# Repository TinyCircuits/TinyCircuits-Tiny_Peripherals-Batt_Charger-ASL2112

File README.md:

# TinyCircuits Tiny Peripheral Battery Charger
# ASL2112 Rev2

The design files are located under design_files/ for the TinyCircuits ASL2112 Rev 2 PCB.  This is a Tiny peripheral board that has a Lithium battery charger and JST SH connector.

Format is in Cadsoft Eagle format - Eagle version 6.2 was used for the original design.

For more infomation on this, check out the product page at TinyCircuits.com: https://tinycircuits.com/collections/accessories/products/tiny-battery-charger

# License:

Design by TinyCircuits.
All design files are released under the Creative Commons Attribution Share-Alike 3.0 License, see the following link for details: http://creativecommons.org/licenses/by-sa/3.0

All text above must be included in any redistribution or derived design

This project uses designs and concepts developed as part of the Arduino project and the LilyPad project.  The TinyCircuits design files themselves (schematics, PCB and libraries) are not directly derived from these works' design files and have been created new, however the concepts and basic architecture behind the TinyDuino and TinyLily products are derived and we thank the hard work of the organizations below for their contributions to open-source hardware:
  
Original Arduino Uno Design by Team Arduino

LilyPad Arduino Design by Leah Buechley and Sparkfun Electronics

Please support the open-source hardware community

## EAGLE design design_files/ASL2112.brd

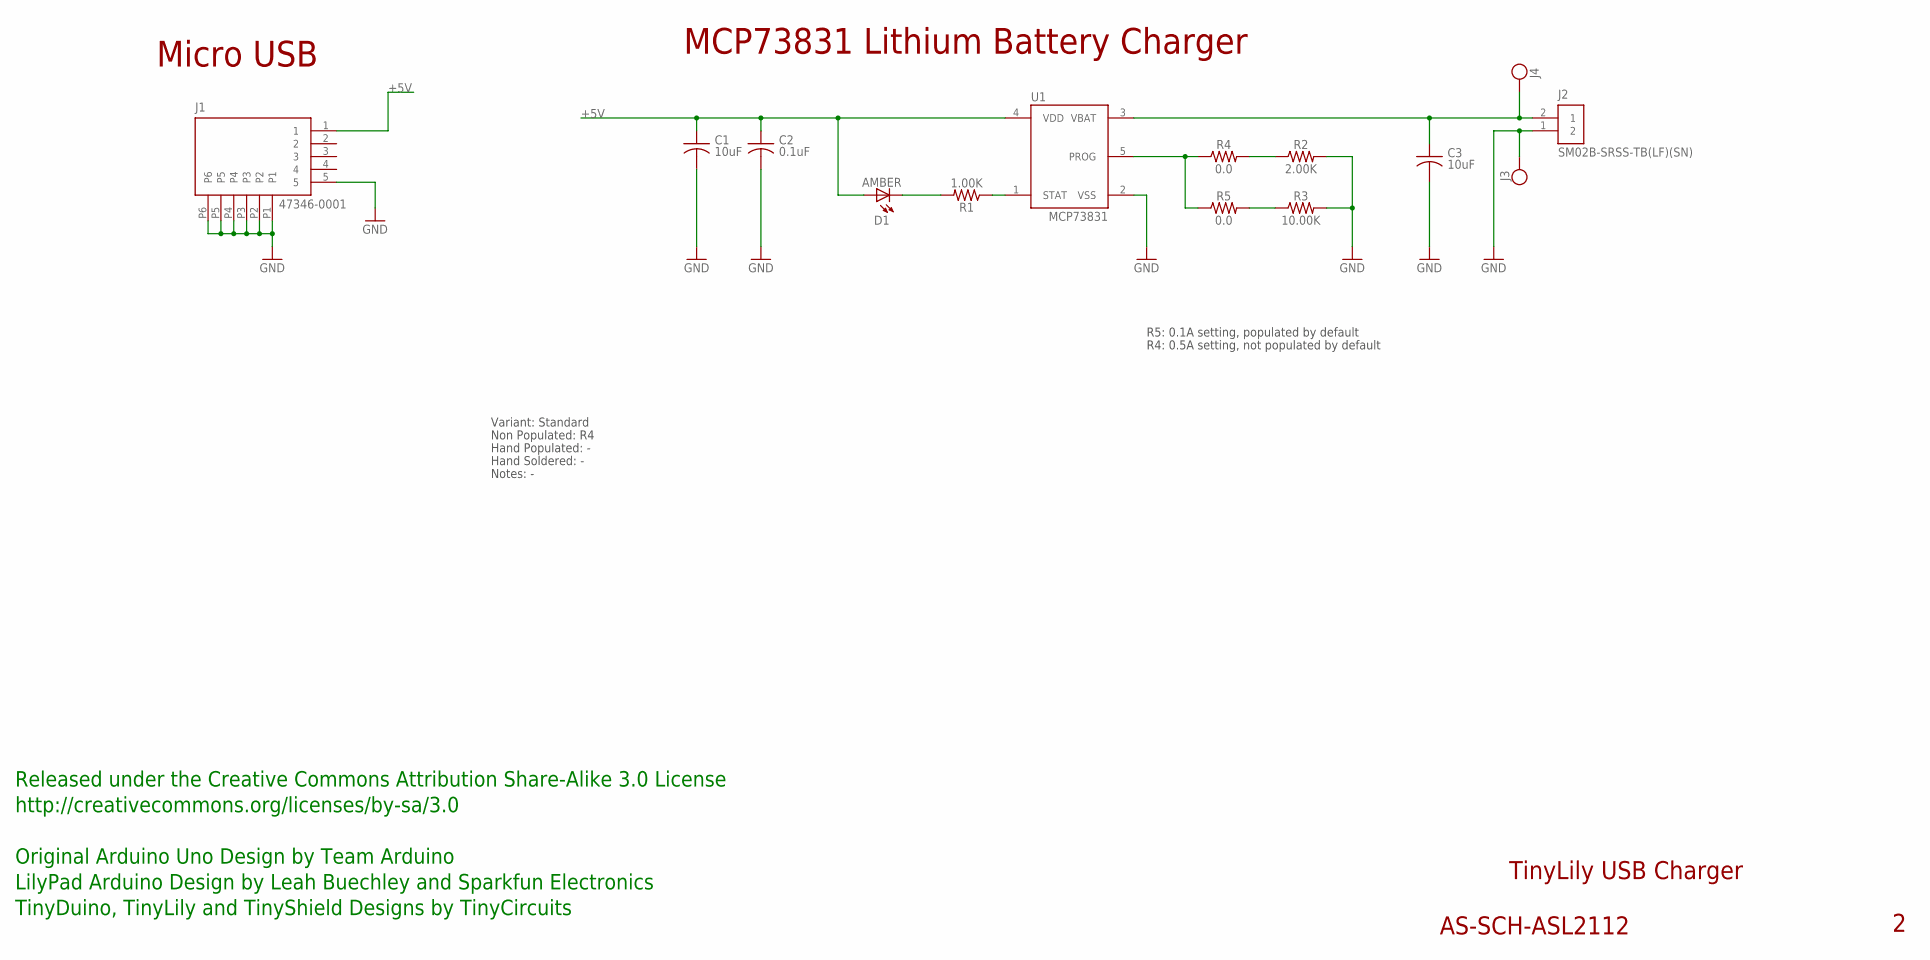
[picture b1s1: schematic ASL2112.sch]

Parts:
C1: 10uF; C0603
C2: 0.1uF; C0402
C3: 10uF; C0603; PARTNO AS-ITM-00002
D1: AMBER; 0402_LED; PARTNO AS-ITM-00058
J1: 47346-0001; MICRO_USB; PARTNO AS-ITM-00021
J2: SM02B-SRSS-TB(LF)(SN); JST_SH_2X1
J3, J4: PIN_1X.1"1; 1X.1"_2
R1: 1.00K; 0402
R2: 2.00K; 0402; PARTNO AS-ITM-00315
R3: 10.00K; 0402; PARTNO AS-ITM-00032
R4, R5: 0.0; 0402
U1: MCP73831; SOT-23

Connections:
+5V: C1.1, C2.1, D1.1 (A), J1.1, U1.4 (VDD)
GND: C1.2, C2.2, C3.2, J1.5, J1.P1, J1.P2, J1.P3, J1.P4, J1.P5, J1.P6, J2.1 (2), J3.1, R2.2, R3.2, U1.2 (VSS)
unnamed: R1.1, U1.1 (STAT)
unnamed: D1.2 (C), R1.2
unnamed: R4.1, R5.1, U1.5 (PROG)
unnamed: R2.1, R4.2
unnamed: C3.1, J2.2 (1), J4.1, U1.3 (VBAT)
unnamed: R3.1, R5.2

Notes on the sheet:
TinyLily USB Charger
AS-SCH-ASL2112
Micro USB
MCP73831 Lithium Battery Charger
Released under the Creative Commons Attribution Share-Alike 3.0 License
http://creativecommons.org/licenses/by-sa/3.0
Original Arduino Uno Design by Team Arduino
TinyDuino, TinyLily and TinyShield Designs by TinyCircuits
LilyPad Arduino Design by Leah Buechley and Sparkfun Electronics
R5: 0.1A setting, populated by default
Non Populated: R4
Hand Populated: -
Hand Soldered: -
Notes: -
Variant: Standard
R4: 0.5A setting, not populated by default

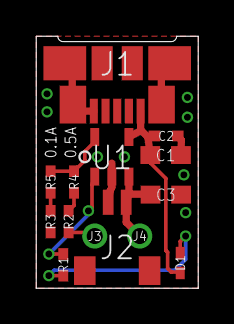
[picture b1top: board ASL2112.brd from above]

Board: 2 copper layers, 9.0 x 14.0 mm, 15 parts (0 on the bottom side), 8 nets.

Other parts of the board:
U$1: DOCFIELD-TINYCIRCUITS-PCB

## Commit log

2016-04-26 :octocat: Added .gitattributes & .gitignore files
2016-04-26 Initial Commit
    Initial Commit
2019-01-04 update format
2020-08-28 Add CAD data
